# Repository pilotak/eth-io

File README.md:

# ETH IO
ESP32 based ethernet I/O board for home automation compatible with ESPHome, Tasmota, etc.

**Features**:
- wide range of input voltage 6-28V
- 4x opto-isolated "fast" operation inputs (connected to GPIO)
- 16x opto-isolated general inputs (connected to MCP23017 expander)
- 2x PWM capable low-side fully protected switches (connected to GPIO)
- 16x low-side fully protected switches for switching the non-latching relays or SSR relays (connected to MCP23017 expander)
- daisy chain design - see below

## Basic wiring

## "Fast" inputs
Are meant to be used for reading pulses from utility meter ie. power meter with S0 output

## Daisy chain design
Should you need more inputs/outputs (up to 96 more inputs/outputs or combination thanks to changing the address of MCP23017) you can use the same PCB. Just don't populate ETH breakout board and ESP32 and solder AMS1117-3.3 with its capacitor. The boards will be connected via SDA/SCL but thanks to a bus buffer (P82B96) communication can easilly be made up to 20 meters (possibly more by reducing speed of I2C bus)!
> In this mode the "slave" device can't make use of S0 inputs nor the PWM outputs

_For more information please visit [wiki](https://github.com/pilotak/eth-io/wiki)_

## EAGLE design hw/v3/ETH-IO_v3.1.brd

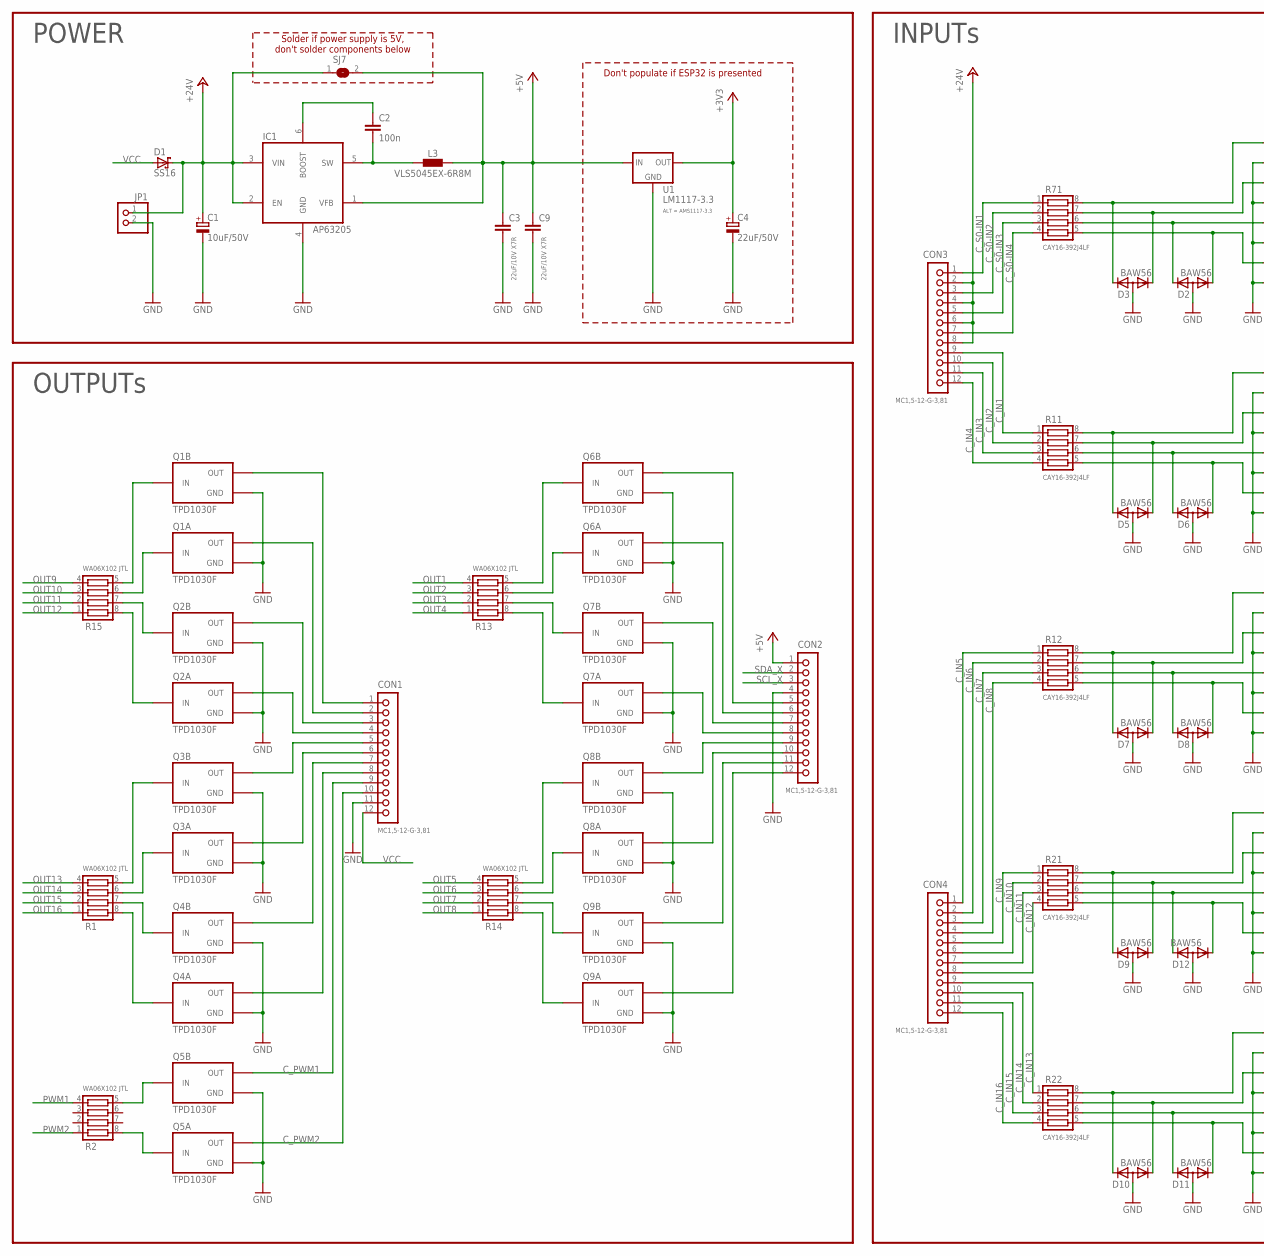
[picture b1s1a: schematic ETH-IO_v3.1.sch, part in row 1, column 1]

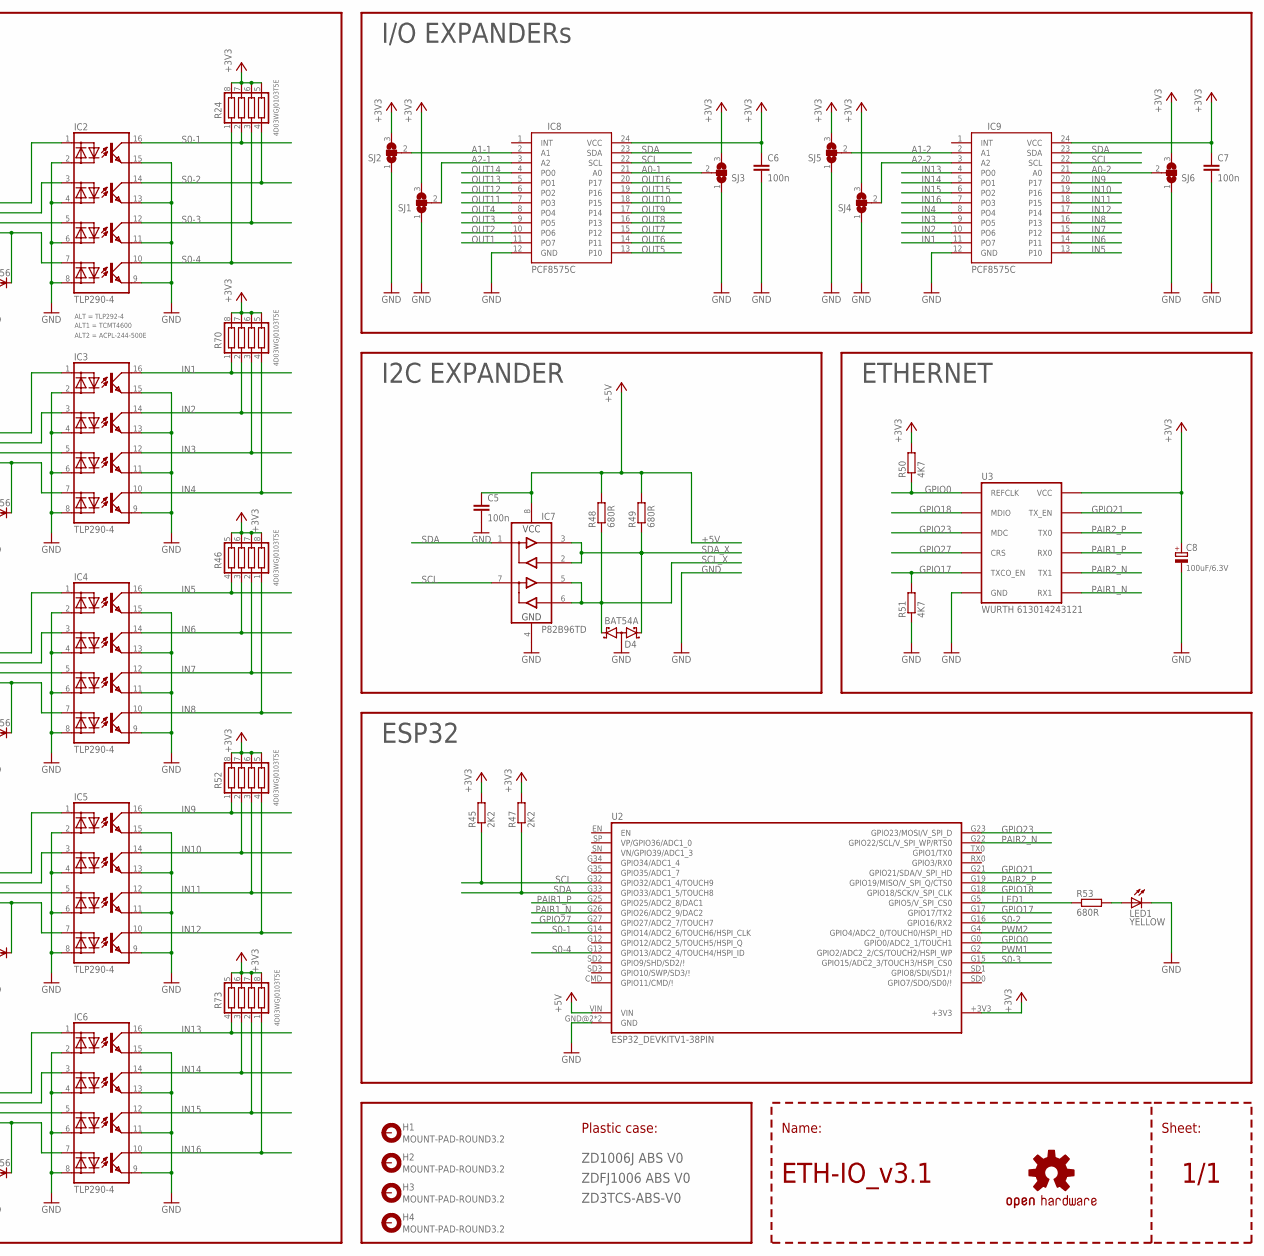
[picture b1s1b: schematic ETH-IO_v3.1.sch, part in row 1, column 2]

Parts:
C1: 10uF/50V; PANASONIC_C
C2, C5, C6, C7: 100n; C0805
C3, C9: 22uF/10V X7R; C1206
C4: 22uF/50V; PANASONIC_C
C8: 100uF/6.3V; PANASONIC_C
CON1, CON2, CON3, CON4: MC1,5-12-G-3,81; MC1,5/12-G-3,81
D1: SS16; DO214AC
D2, D3, D5, D6, D7, D8, D9, D10, D11, D12: BAW56; SOT23
D4: BAT54A; SOT23
H1, H2, H3, H4: MOUNT-PAD-ROUND3.2; 3,2-PAD
IC1: AP63205; SOT23-6
IC2, IC3, IC4, IC5, IC6: TLP290-4; SO16
IC7: P82B96TD; SO08
IC8, IC9: PCF8575C; SO-24DW
JP1: PINHD-1X2; 1X02
L3: VLS5045EX-6R8M; L5040-LONGER
LED1: YELLOW; LED0805
LOGO1: OSHW-LOGOM-COPPER; OSHW-LOGO-M_COPPER
Q1, Q2, Q3, Q4, Q5, Q6, Q7, Q8, Q9: TPD1030F; SO8
R1, R2, R13, R14, R15: WA06X102 JTL; RESCAV80P320X160X60-8N
R11, R12, R21, R22, R71: CAY16-392J4LF; RESCAV80P320X160X60-8N
R24, R46, R52, R70, R73: 4D03WGJ0103T5E; RESCAV80P320X160X60-8N
R45, R47: 2K2; R0805
R48, R49, R53: 680R; R0805
R50, R51: 4K7; R0805
SJ1, SJ2, SJ3, SJ4, SJ5, SJ6: SJ2W; SJ_2
SJ7: SJ
U1: LM1117-3.3; SOT223
U2: ESP32_DEVKITV1-38PIN; ESP32_DEVKITV1_38PIN
U3: WURTH 613014243121; LAN8720_ETH_BOARD

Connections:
+3V3: C4.+, C6.1, C7.1, C8.+, IC8.24 (VCC), IC9.24 (VCC), R24.5 (4), R24.6 (3), R24.7 (2), R24.8 (1), R45.2, R46.5 (4), R46.6 (3), R46.7 (2), R46.8 (1), R47.2, R50.2, R52.5 (4), R52.6 (3), R52.7 (2), R52.8 (1), R70.5 (4), R70.6 (3), R70.7 (2), R70.8 (1), R73.5 (4), R73.6 (3), R73.7 (2), R73.8 (1), SJ1.3, SJ2.3, SJ3.3, SJ4.3, SJ5.3, SJ6.3, U1.2 (OUT), U1.4 (OUT), U2.+3V3, U3.VCC, U3.VCC@1 (VCC)
+5V: C3.1, C5.1, C9.1, CON2.1, IC1.1 (VFB), IC7.8 (VCC), L3.1, R48.2, R49.2, SJ7.2, U1.3 (IN), U2.VIN
+24V: C1.+, CON3.2, CON3.4, CON3.6, CON3.8, D1.C, IC1.2 (EN), IC1.3 (VIN), JP1.1, SJ7.1
A0-1: IC8.21 (A0), SJ3.2
A0-2: IC9.21 (A0), SJ6.2
A1-1: IC8.2 (A1), SJ2.2
A1-2: IC9.2 (A1), SJ5.2
A2-1: IC8.3 (A2), SJ1.2
A2-2: IC9.3 (A2), SJ4.2
C_IN1: CON3.9, R11.1
C_IN2: CON3.10, R11.2
C_IN3: CON3.11, R11.3
C_IN4: CON3.12, R11.4
C_IN5: CON4.1, R12.1
C_IN6: CON4.2, R12.2
C_IN7: CON4.3, R12.3
C_IN8: CON4.4, R12.4
C_IN9: CON4.5, R21.1
C_IN10: CON4.6, R21.2
C_IN11: CON4.7, R21.3
C_IN12: CON4.8, R21.4
C_IN13: CON4.9, R22.1
C_IN14: CON4.10, R22.2
C_IN15: CON4.11, R22.3
C_IN16: CON4.12, R22.4
C_OUT1: CON2.5, Q6.5 (OUT), Q6.6 (OUT)
C_OUT2: CON2.6, Q6.7 (OUT), Q6.8 (OUT)
C_OUT3: CON2.7, Q7.5 (OUT), Q7.6 (OUT)
C_OUT4: CON2.8, Q7.7 (OUT), Q7.8 (OUT)
C_OUT5: CON2.9, Q8.5 (OUT), Q8.6 (OUT)
C_OUT6: CON2.10, Q8.7 (OUT), Q8.8 (OUT)
C_OUT7: CON2.11, Q9.5 (OUT), Q9.6 (OUT)
C_OUT8: CON2.12, Q9.7 (OUT), Q9.8 (OUT)
C_OUT9: CON1.1, Q1.5 (OUT), Q1.6 (OUT)
C_OUT10: CON1.2, Q1.7 (OUT), Q1.8 (OUT)
C_OUT11: CON1.3, Q2.5 (OUT), Q2.6 (OUT)
C_OUT12: CON1.4, Q2.7 (OUT), Q2.8 (OUT)
C_OUT13: CON1.5, Q3.5 (OUT), Q3.6 (OUT)
C_OUT14: CON1.6, Q3.7 (OUT), Q3.8 (OUT)
C_OUT15: CON1.7, Q4.5 (OUT), Q4.6 (OUT)
C_OUT16: CON1.8, Q4.7 (OUT), Q4.8 (OUT)
C_PWM1: CON1.9, Q5.5 (OUT), Q5.6 (OUT)
C_PWM2: CON1.10, Q5.7 (OUT), Q5.8 (OUT)
C_S0-IN1: CON3.1, R71.1
C_S0-IN2: CON3.3, R71.2
C_S0-IN3: CON3.5, R71.3
C_S0-IN4: CON3.7, R71.4
GND: C1.-, C3.2, C4.-, C5.2, C6.2, C7.2, C8.-, C9.2, CON1.11, CON2.4, D2.3 (A), D3.3 (A), D4.3 (AA), D5.3 (A), D6.3 (A), D7.3 (A), D8.3 (A), D9.3 (A), D10.3 (A), D11.3 (A), D12.3 (A), IC1.4 (GND), IC2.2 (C1), IC2.4 (C2), IC2.6 (C3), IC2.8 (C4), IC2.9 (EMIT4), IC2.11 (EMIT3), IC2.13 (EMIT2), IC2.15 (EMIT1), IC3.2 (C1), IC3.4 (C2), IC3.6 (C3), IC3.8 (C4), IC3.9 (EMIT4), IC3.11 (EMIT3), IC3.13 (EMIT2), IC3.15 (EMIT1), IC4.2 (C1), IC4.4 (C2), IC4.6 (C3), IC4.8 (C4), IC4.9 (EMIT4), IC4.11 (EMIT3), IC4.13 (EMIT2), IC4.15 (EMIT1), IC5.2 (C1), IC5.4 (C2), IC5.6 (C3), IC5.8 (C4), IC5.9 (EMIT4), IC5.11 (EMIT3), IC5.13 (EMIT2), IC5.15 (EMIT1), IC6.2 (C1), IC6.4 (C2), IC6.6 (C3), IC6.8 (C4), IC6.9 (EMIT4), IC6.11 (EMIT3), IC6.13 (EMIT2), IC6.15 (EMIT1), IC7.4 (GND), IC8.12 (GND), IC9.12 (GND), JP1.2, LED1.C, Q1.1 (GND), Q1.3 (GND), Q2.1 (GND), Q2.3 (GND), Q3.1 (GND), Q3.3 (GND), Q4.1 (GND), Q4.3 (GND), Q5.1 (GND), Q5.3 (GND), Q6.1 (GND), Q6.3 (GND), Q7.1 (GND), Q7.3 (GND), Q8.1 (GND), Q8.3 (GND), Q9.1 (GND), Q9.3 (GND), R51.1, SJ1.1, SJ2.1, SJ3.1, SJ4.1, SJ5.1, SJ6.1, U1.1 (GND), U2.GND@2 (GND), U2.GND@3 (GND), U3.GND, U3.GND@1 (GND)
GPIO0: R50.1, U2.G0 (GPIO0/ADC2_1/TOUCH1), U3.INT (REFCLK)
GPIO17: R51.2, U2.G17 (GPIO17/TX2), U3.TXCO_EN
GPIO18: U2.G18 (GPIO18/SCK/V_SPI_CLK), U3.MDIO
GPIO21: U2.G21 (GPIO21/SDA/V_SPI_HD), U3.TX_EN
GPIO23: U2.G23 (GPIO23/MOSI/V_SPI_D), U3.MDC
GPIO27: U2.G27 (GPIO27/ADC2_7/TOUCH7), U3.CRS
IN1: IC3.16 (COL1), IC9.11 (PO7), R70.1
IN2: IC3.14 (COL2), IC9.10 (PO6), R70.2
IN3: IC3.12 (COL3), IC9.9 (PO5), R70.3
IN4: IC3.10 (COL4), IC9.8 (PO4), R70.4
IN5: IC4.16 (COL1), IC9.13 (P10), R46.4
IN6: IC4.14 (COL2), IC9.14 (P11), R46.3
IN7: IC4.12 (COL3), IC9.15 (P12), R46.2
IN8: IC4.10 (COL4), IC9.16 (P13), R46.1
IN9: IC5.16 (COL1), IC9.20 (P17), R52.1
IN10: IC5.14 (COL2), IC9.19 (P16), R52.2
IN11: IC5.12 (COL3), IC9.18 (P15), R52.3
IN12: IC5.10 (COL4), IC9.17 (P14), R52.4
IN13: IC6.16 (COL1), IC9.4 (PO0), R73.4
IN14: IC6.14 (COL2), IC9.5 (PO1), R73.3
IN15: IC6.12 (COL3), IC9.6 (PO2), R73.2
IN16: IC6.10 (COL4), IC9.7 (PO3), R73.1
LED1: R53.1, U2.G5 (GPIO5/V_SPI_CS0)
LED_RED: LED1.A, R53.2
unnamed: D3.2 (K2), IC2.1 (A1), R71.8 (1)
unnamed: D3.1 (K1), IC2.3 (A2), R71.7 (2)
unnamed: Q1.2 (IN), R15.6 (3)
unnamed: Q1.4 (IN), R15.5 (4)
unnamed: D2.2 (K2), IC2.5 (A3), R71.6 (3)
unnamed: D2.1 (K1), IC2.7 (A4), R71.5 (4)
unnamed: D5.2 (K2), IC3.1 (A1), R11.8 (1)
unnamed: Q5.4 (IN), R2.5 (4)
unnamed: Q5.2 (IN), R2.8 (1)
unnamed: D6.1 (K1), IC3.7 (A4), R11.5 (4)
unnamed: D5.1 (K1), IC3.3 (A2), R11.7 (2)
unnamed: D6.2 (K2), IC3.5 (A3), R11.6 (3)
unnamed: D7.2 (K2), IC4.1 (A1), R12.8 (1)
unnamed: D7.1 (K1), IC4.3 (A2), R12.7 (2)
unnamed: D8.2 (K2), IC4.5 (A3), R12.6 (3)
unnamed: D8.1 (K1), IC4.7 (A4), R12.5 (4)
unnamed: D12.2 (K2), IC5.5 (A3), R21.6 (3)
unnamed: D12.1 (K1), IC5.7 (A4), R21.5 (4)
unnamed: D9.1 (K1), IC5.3 (A2), R21.7 (2)
unnamed: D9.2 (K2), IC5.1 (A1), R21.8 (1)
unnamed: D11.2 (K2), IC6.5 (A3), R22.6 (3)
unnamed: D11.1 (K1), IC6.7 (A4), R22.5 (4)
unnamed: D10.1 (K1), IC6.3 (A2), R22.7 (2)
unnamed: D10.2 (K2), IC6.1 (A1), R22.8 (1)
unnamed: Q2.4 (IN), R15.7 (2)
unnamed: Q2.2 (IN), R15.8 (1)
unnamed: Q3.4 (IN), R1.5 (4)
unnamed: Q3.2 (IN), R1.6 (3)
unnamed: Q4.4 (IN), R1.7 (2)
unnamed: Q4.2 (IN), R1.8 (1)
unnamed: Q6.4 (IN), R13.5 (4)
unnamed: Q6.2 (IN), R13.6 (3)
unnamed: Q7.4 (IN), R13.7 (2)
unnamed: Q7.2 (IN), R13.8 (1)
unnamed: Q8.4 (IN), R14.5 (4)
unnamed: Q8.2 (IN), R14.6 (3)
unnamed: Q9.4 (IN), R14.7 (2)
unnamed: Q9.2 (IN), R14.8 (1)
unnamed: C2.2, IC1.5 (SW), L3.2
unnamed: C2.1, IC1.6 (BOOST)
OUT1: IC8.11 (PO7), R13.4
OUT2: IC8.10 (PO6), R13.3
OUT3: IC8.9 (PO5), R13.2
OUT4: IC8.8 (PO4), R13.1
OUT5: IC8.13 (P10), R14.4
OUT6: IC8.14 (P11), R14.3
OUT7: IC8.15 (P12), R14.2
OUT8: IC8.16 (P13), R14.1
OUT9: IC8.17 (P14), R15.4
OUT10: IC8.18 (P15), R15.3
OUT11: IC8.7 (PO3), R15.2
OUT12: IC8.6 (PO2), R15.1
OUT13: IC8.5 (PO1), R1.4
OUT14: IC8.4 (PO0), R1.3
OUT15: IC8.19 (P16), R1.2
OUT16: IC8.20 (P17), R1.1
PAIR1_N: U2.G26 (GPIO26/ADC2_9/DAC2), U3.RX1
PAIR1_P: U2.G25 (GPIO25/ADC2_8/DAC1), U3.RX0
PAIR2_N: U2.G22 (GPIO22/SCL/V_SPI_WP/RTS0), U3.TX1
PAIR2_P: U2.G19 (GPIO19/MISO/V_SPI_Q/CTS0), U3.TX0
PWM1: R2.4, U2.G2 (GPIO2/ADC2_2/CS/TOUCH2/HSPI_WP)
PWM2: R2.1, U2.G4 (GPIO4/ADC2_0/TOUCH0/HSPI_HD)
S0-1: IC2.16 (COL1), R24.2, U2.G14 (GPIO14/ADC2_6/TOUCH6/HSPI_CLK)
S0-2: IC2.14 (COL2), R24.4, U2.G16 (GPIO16/RX2)
S0-3: IC2.12 (COL3), R24.3, U2.G15 (GPIO15/ADC2_3/TOUCH3/HSPI_CS0)
S0-4: IC2.10 (COL4), R24.1, U2.G13 (GPIO13/ADC2_4/TOUCH4/HSPI_ID)
SCL: IC7.7 (SY), IC8.22 (SCL), IC9.22 (SCL), R45.1, U2.G32 (GPIO32/ADC1_4/TOUCH9)
SCL_X: CON2.3, D4.1 (K1), IC7.5 (TY), IC7.6 (RY), R48.1
SDA: IC7.1 (SX), IC8.23 (SDA), IC9.23 (SDA), R47.1, U2.G33 (GPIO33/ADC1_5/TOUCH8)
SDA_X: CON2.2, D4.2 (K2), IC7.2 (RX), IC7.3 (TX), R49.1
VCC: CON1.12, D1.A

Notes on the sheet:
INPUTs
OUTPUTs
POWER
I2C EXPANDER
ETHERNET
ZDFJ1006 ABS V0
ZD3TCS-ABS-V0
ZD1006J ABS V0
Don't populate if ESP32 is presented
ESP32
ETH-IO_v3.1
Sheet:
Name:
Plastic case:
I/O EXPANDERs
Solder if power supply is 5V, don't solder components below

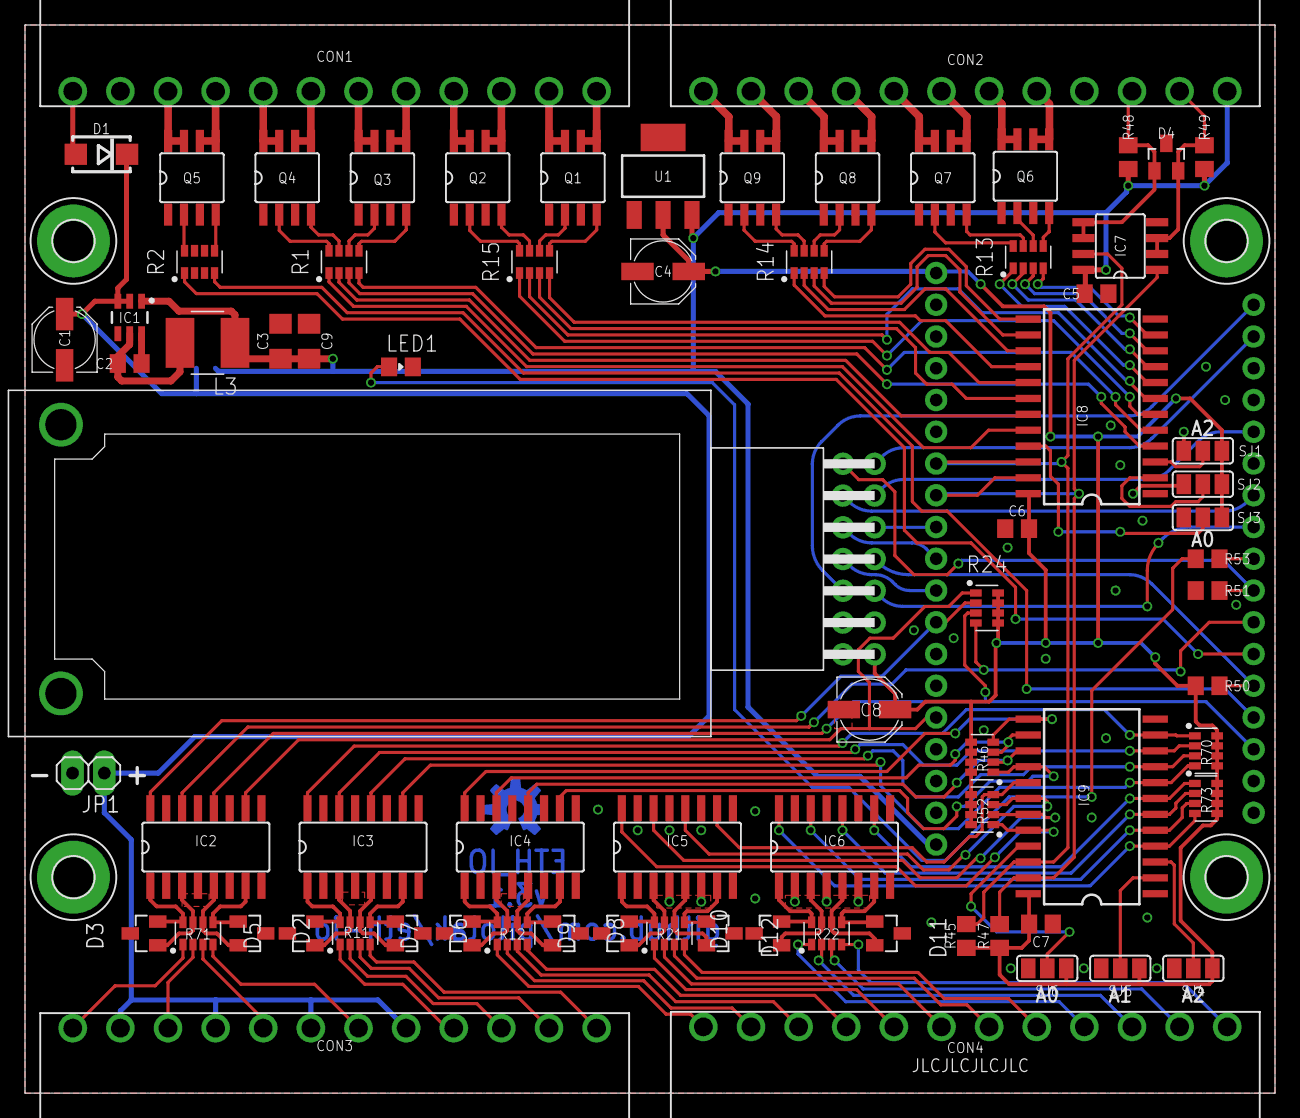
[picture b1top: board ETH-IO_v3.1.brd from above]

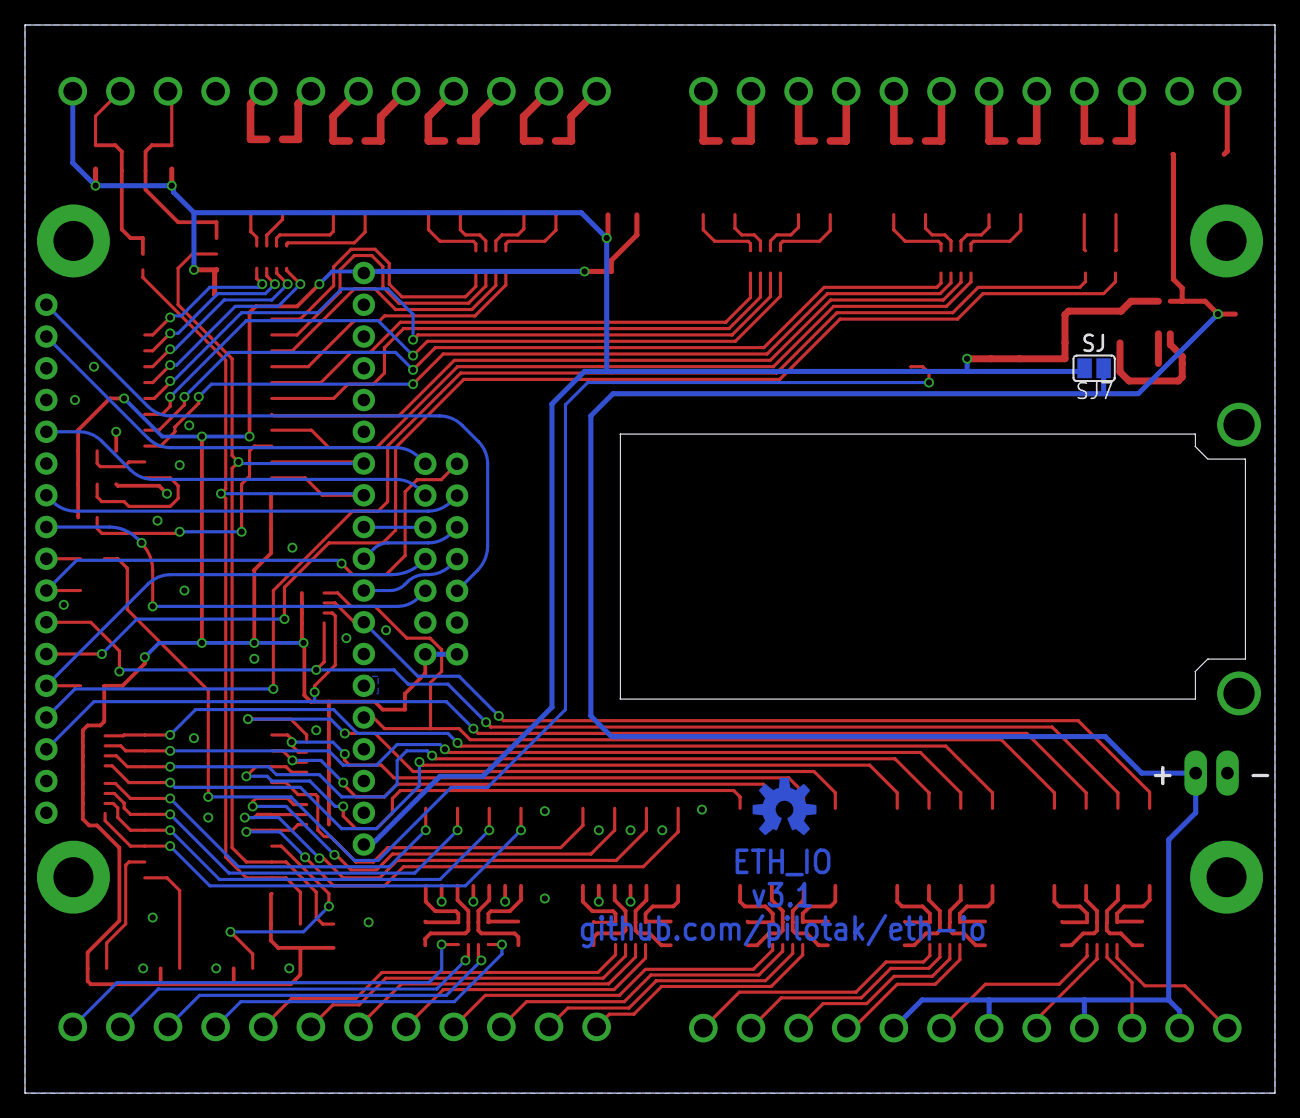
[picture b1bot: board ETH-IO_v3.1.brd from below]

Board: 2 copper layers, 100.0 x 85.4 mm, 83 parts (2 on the bottom side), 143 nets.

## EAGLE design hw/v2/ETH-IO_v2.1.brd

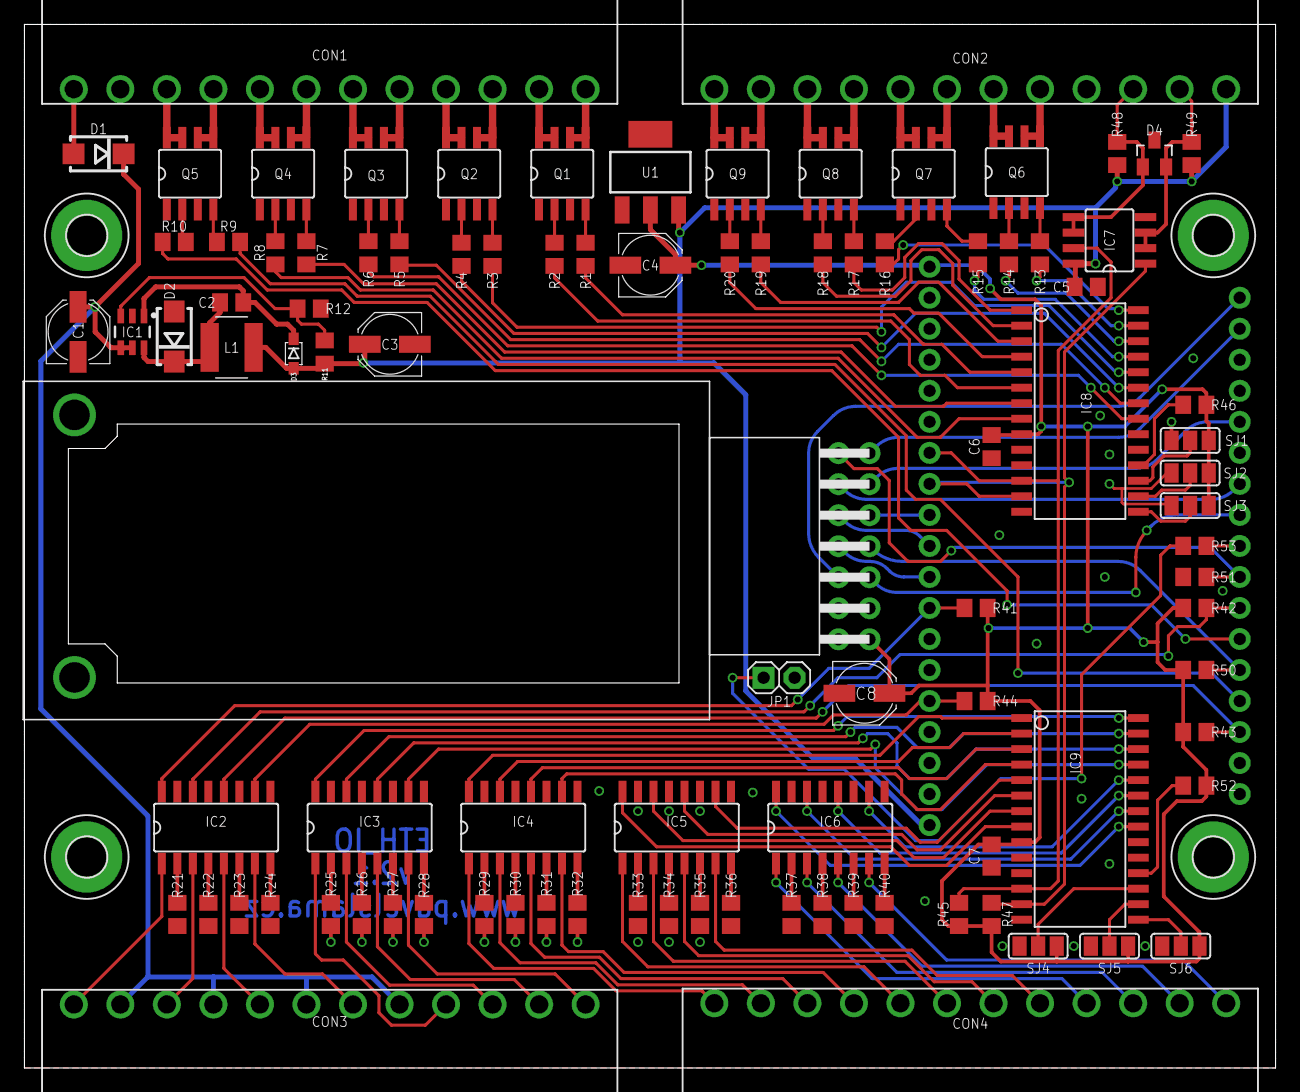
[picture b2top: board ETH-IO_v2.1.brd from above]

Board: 2 copper layers, 102.4 x 85.4 mm, 102 parts (0 on the bottom side), 146 nets.

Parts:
C1, C3, C4: 22uF/50V; PANASONIC_C
C2, C5, C6, C7: 100n; C0805
C8: 100uF/6.3V; PANASONIC_C
CON1, CON2, CON3, CON4: MC1,5-12-G-3,81; MC1,5/12-G-3,81
D1, D2: SS16; DO214AC
D3: 1N4148WS; SOD323
D4: BAT54A; SOT23
H1, H2, H3, H4: MOUNT-PAD-ROUND3.2; 3,2-PAD
IC1: MCP16301T-I/CH; SOT23-6
IC2, IC3, IC4, IC5, IC6: TLP290-4; SO16
IC7: P82B96TD; SO08
IC8, IC9: MCP23017-E/SO; SO28W
JP1: 1X02-S
L1: SRN5040-220M; L5040
Q1, Q2, Q3, Q4, Q5, Q6, Q7, Q8, Q9: BTS3410G; SO8
R1, R2, R3, R4, R5, R6, R7, R8, R9, R10, R13, R14, R15, R16, R17, R18, R19, R20, R46, R52: 1K; R0805
R11: 52K3; R0805
R12: 10K 1%; R0805
R21, R22, R23, R24, R25, R26, R27, R28, R29, R30, R31, R32, R33, R34, R35, R36, R37, R38, R39, R40: 3K9; R0805
R41, R42, R43, R44: 10K; R0805
R45, R47: 2K2; R0805
R48, R49, R53: 680R; R0805
R50, R51: 4K7; R0805
SJ1, SJ2, SJ3, SJ4, SJ5, SJ6: SJ_2
U1: LM1117-3.3; SOT223
U2: ESP32_DEVKITV1-38PIN; ESP32_DEVKITV1_38PIN
U3: WURTH 613014243121; LAN8720_ETH_BOARD

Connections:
+3V3: C4.+, C6.1, C7.1, C8.+, IC8.9, IC9.9, R41.2, R42.2, R43.2, R44.2, R45.2, R46.2, R47.2, R50.2, R52.2, SJ1.3, SJ2.3, SJ3.3, SJ4.3, SJ5.3, SJ6.3, U1.2, U1.4, U2.+3V3, U3.VCC, U3.VCC@1
+5V: C3.+, C5.1, CON2.1, D3.A, IC7.8, L1.1, R11.2, R48.2, R49.2, U1.3, U2.VIN
+24V: C1.+, CON3.2, CON3.4, CON3.6, CON3.8, D1.C, IC1.4, IC1.5
C_IN1: CON3.9, IC3.1
C_IN2: CON3.10, IC3.3
C_IN3: CON3.11, IC3.5
C_IN4: CON3.12, IC3.7
C_IN5: CON4.1, IC4.1
C_IN6: CON4.2, IC4.3
C_IN7: CON4.3, IC4.5
C_IN8: CON4.4, IC4.7
C_IN9: CON4.5, IC5.1
C_IN10: CON4.6, IC5.3
C_IN11: CON4.7, IC5.5
C_IN12: CON4.8, IC5.7
C_IN13: CON4.9, IC6.1
C_IN14: CON4.10, IC6.3
C_IN15: CON4.11, IC6.5
C_IN16: CON4.12, IC6.7
C_OUT1: CON2.5, Q6.5, Q6.6
C_OUT2: CON2.6, Q6.7, Q6.8
C_OUT3: CON2.7, Q7.5, Q7.6
C_OUT4: CON2.8, Q7.7, Q7.8
C_OUT5: CON2.9, Q8.5, Q8.6
C_OUT6: CON2.10, Q8.7, Q8.8
C_OUT7: CON2.11, Q9.5, Q9.6
C_OUT8: CON2.12, Q9.7, Q9.8
C_OUT9: CON1.1, Q1.5, Q1.6
C_OUT10: CON1.2, Q1.7, Q1.8
C_OUT11: CON1.3, Q2.5, Q2.6
C_OUT12: CON1.4, Q2.7, Q2.8
C_OUT13: CON1.5, Q3.5, Q3.6
C_OUT14: CON1.6, Q3.7, Q3.8
C_OUT15: CON1.7, Q4.5, Q4.6
C_OUT16: CON1.8, Q4.7, Q4.8
C_PWM1: CON1.9, Q5.5, Q5.6
C_PWM2: CON1.10, Q5.7, Q5.8
C_S0-IN1: CON3.1, IC2.1
C_S0-IN2: CON3.3, IC2.3
C_S0-IN3: CON3.5, IC2.5
C_S0-IN4: CON3.7, IC2.7
GND: C1.-, C3.-, C4.-, C5.2, C6.2, C7.2, C8.-, CON1.11, CON2.4, D2.A, D4.3, IC1.2, IC2.9, IC2.11, IC2.13, IC2.15, IC3.9, IC3.11, IC3.13, IC3.15, IC4.9, IC4.11, IC4.13, IC4.15, IC5.9, IC5.11, IC5.13, IC5.15, IC6.9, IC6.11, IC6.13, IC6.15, IC7.4, IC8.10, IC9.10, JP1.2, Q1.1, Q1.3, Q2.1, Q2.3, Q3.1, Q3.3, Q4.1, Q4.3, Q5.1, Q5.3, Q6.1, Q6.3, Q7.1, Q7.3, Q8.1, Q8.3, Q9.1, Q9.3, R12.1, R21.1, R22.1, R23.1, R24.1, R25.1, R26.1, R27.1, R28.1, R29.1, R30.1, R31.1, R32.1, R33.1, R34.1, R35.1, R36.1, R37.1, R38.1, R39.1, R40.1, R51.1, SJ1.1, SJ2.1, SJ3.1, SJ4.1, SJ5.1, SJ6.1, U1.1, U2.GND@2, U2.GND@3, U3.GND, U3.GND@1
GPIO0: R50.1, U2.G0, U3.INT
GPIO17: R51.2, U2.G17, U3.TXCO_EN
GPIO18: U2.G18, U3.MDIO
GPIO21: U2.G21, U3.TX_EN
GPIO23: U2.G23, U3.MDC
GPIO27: U2.G27, U3.CRS
IN1: IC3.16, IC9.28
IN2: IC3.14, IC9.27
IN3: IC3.12, IC9.26
IN4: IC3.10, IC9.25
IN5: IC4.16, IC9.1
IN6: IC4.14, IC9.2
IN7: IC4.12, IC9.3
IN8: IC4.10, IC9.4
IN9: IC5.16, IC9.8
IN10: IC5.14, IC9.7
IN11: IC5.12, IC9.6
IN12: IC5.10, IC9.5
IN13: IC6.16, IC9.21
IN14: IC6.14, IC9.22
IN15: IC6.12, IC9.23
IN16: IC6.10, IC9.24
LED1: R53.1, U2.G5
LED_RED: JP1.1, R53.2
unnamed: IC9.15, SJ6.2
unnamed: IC8.16, SJ2.2
unnamed: Q1.2, R2.2
unnamed: Q1.4, R1.2
unnamed: IC8.18, R46.1
unnamed: IC9.18, R52.1
unnamed: IC8.15, SJ3.2
unnamed: Q5.4, R9.2
unnamed: Q5.2, R10.2
unnamed: IC9.16, SJ5.2
unnamed: IC3.2, R25.2
unnamed: IC3.4, R26.2
unnamed: IC3.6, R27.2
unnamed: IC3.8, R28.2
unnamed: IC4.2, R29.2
unnamed: IC4.4, R30.2
unnamed: IC4.6, R31.2
unnamed: IC4.8, R32.2
unnamed: IC5.2, R33.2
unnamed: IC5.4, R34.2
unnamed: IC5.6, R35.2
unnamed: IC5.8, R36.2
unnamed: IC6.2, R37.2
unnamed: IC6.4, R38.2
unnamed: IC6.6, R39.2
unnamed: IC6.8, R40.2
unnamed: IC9.17, SJ4.2
unnamed: Q2.4, R3.2
unnamed: Q2.2, R4.2
unnamed: IC8.17, SJ1.2
unnamed: Q3.4, R5.2
unnamed: Q3.2, R6.2
unnamed: Q4.4, R7.2
unnamed: Q4.2, R8.2
unnamed: IC2.2, R21.2
unnamed: Q6.4, R13.2
unnamed: Q6.2, R14.2
unnamed: Q7.4, R15.2
unnamed: Q7.2, R16.2
unnamed: Q8.4, R17.2
unnamed: Q8.2, R18.2
unnamed: Q9.4, R19.2
unnamed: Q9.2, R20.2
unnamed: IC2.4, R22.2
unnamed: IC2.6, R23.2
unnamed: IC2.8, R24.2
unnamed: C2.2, D2.C, IC1.6, L1.2
unnamed: C2.1, D3.C, IC1.1
unnamed: IC1.3, R11.1, R12.2
OUT1: IC8.27, R13.1
OUT2: IC8.26, R14.1
OUT3: IC8.25, R15.1
OUT4: IC8.28, R16.1
OUT5: IC8.1, R17.1
OUT6: IC8.2, R18.1
OUT7: IC8.3, R19.1
OUT8: IC8.4, R20.1
OUT9: IC8.5, R1.1
OUT10: IC8.6, R2.1
OUT11: IC8.24, R3.1
OUT12: IC8.23, R4.1
OUT13: IC8.22, R5.1
OUT14: IC8.21, R6.1
OUT15: IC8.7, R7.1
OUT16: IC8.8, R8.1
PAIR1_N: U2.G26, U3.RX1
PAIR1_P: U2.G25, U3.RX0
PAIR2_N: U2.G22, U3.TX1
PAIR2_P: U2.G19, U3.TX0
PWM1: R9.1, U2.G2
PWM2: R10.1, U2.G4
S0-1: IC2.16, R41.1, U2.G14
S0-2: IC2.14, R42.1, U2.G16
S0-3: IC2.12, R43.1, U2.G15
S0-4: IC2.10, R44.1, U2.G13
SCL: IC7.7, IC8.12, IC9.12, R45.1, U2.G32
SCL_X: CON2.3, D4.1, IC7.5, IC7.6, R48.1
SDA: IC7.1, IC8.13, IC9.13, R47.1, U2.G33
SDA_X: CON2.2, D4.2, IC7.2, IC7.3, R49.1
VCC: CON1.12, D1.A

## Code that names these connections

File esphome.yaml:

esphome:
  name: eth_io
  platform: ESP32
  board: nodemcu-32s

ethernet:
  type: LAN8720
  mdc_pin: GPIO23
  mdio_pin: GPIO18
  phy_addr: 1
  clk_mode: GPIO0_IN
  power_pin: GPIO17

logger:

ota:

api:

i2c:
  sda: GPIO33
  scl: GPIO32
  frequency: 100kHz

mcp23017:
  - id: out_hub1
    address: 0x20

  - id: in_hub1
    address: 0x21

time:
  - platform: homeassistant
    id: homeassistant_time
    timezone: "Europe/Prague"

status_led:
  pin:
    number: GPIO5

sensor:
  - platform: pulse_counter
    pin: GPIO14
    name: "Power consumption 1"
    id: power1
    unit_of_measurement: 'Wh'
    internal_filter: 13us
    filters:
      - multiply: 16.66666666666
    count_mode:
      rising_edge: DISABLE
      falling_edge: INCREMENT

  - platform: pulse_counter
    pin: GPIO16
    name: "Power consumption 2"
    id: power2
    unit_of_measurement: 'Wh'
    internal_filter: 13us
    filters:
      - multiply: 16.66666666666
    count_mode:
      rising_edge: DISABLE
      falling_edge: INCREMENT

  - platform: pulse_counter
    pin: GPIO15
    name: "Power consumption 3"
    id: power3
    unit_of_measurement: 'Wh'
    internal_filter: 13us
    filters:
      - multiply: 16.66666666666
    count_mode:
      rising_edge: DISABLE
      falling_edge: INCREMENT

  - platform: pulse_counter
    pin: GPIO13
    name: "Power consumption 4"
    id: power4
    unit_of_measurement: 'Wh'
    internal_filter: 13us
    filters:
      - multiply: 16.66666666666
    count_mode:
      rising_edge: DISABLE
      falling_edge: INCREMENT

  - platform: total_daily_energy
    name: "Daily power consumption 1"
    icon: "mdi:current-ac"
    power_id: power1
    unit_of_measurement: 'kWh'
    filters:
      - multiply: 0.001

  - platform: total_daily_energy
    name: "Daily power consumption 2"
    icon: "mdi:current-ac"
    power_id: power2
    unit_of_measurement: 'kWh'
    filters:
      - multiply: 0.001

  - platform: total_daily_energy
    name: "Daily power consumption 3"
    icon: "mdi:current-ac"
    power_id: power3
    unit_of_measurement: 'kWh'
    filters:
      - multiply: 0.001

  - platform: total_daily_energy
    name: "Daily power consumption 4"
    icon: "mdi:current-ac"
    power_id: power4
    unit_of_measurement: 'kWh'
    filters:
      - multiply: 0.001

binary_sensor:
  - platform: gpio
    id: in1
    pin:
      mcp23017: in_hub1
      number: 7
      mode: INPUT_PULLUP
      inverted: True
    filters:
      - delayed_on: 3ms
      - delayed_off: 3ms
    on_click:
      then:
        - switch.toggle: output1

  - platform: gpio
    id: in2
    pin:
      mcp23017: in_hub1
      number: 6
      mode: INPUT_PULLUP
      inverted: True
    filters:
      - delayed_on: 3ms
      - delayed_off: 3ms
    on_click:
      then:
        - switch.toggle: output2

  - platform: gpio
    id: in3
    pin:
      mcp23017: in_hub1
      number: 5
      mode: INPUT_PULLUP
      inverted: True
    filters:
      - delayed_on: 3ms
      - delayed_off: 3ms
    on_click:
      then:
        - switch.toggle: output3

  - platform: gpio
    id: in4
    pin:
      mcp23017: in_hub1
      number: 4
      mode: INPUT_PULLUP
      inverted: True
    filters:
      - delayed_on: 3ms
      - delayed_off: 3ms
    on_click:
      then:
        - switch.toggle: output4

  - platform: gpio
    id: in5
    pin:
      mcp23017: in_hub1
      number: 8
      mode: INPUT_PULLUP
      inverted: True
    filters:
      - delayed_on: 3ms
      - delayed_off: 3ms
    on_click:
      then:
        - switch.toggle: output5

  - platform: gpio
    id: in6
    pin:
      mcp23017: in_hub1
      number: 9
      mode: INPUT_PULLUP
      inverted: True
    filters:
      - delayed_on: 3ms
      - delayed_off: 3ms
    on_click:
      then:
        - switch.toggle: output6

  - platform: gpio
    id: in7
    pin:
      mcp23017: in_hub1
      number: 10
      mode: INPUT_PULLUP
      inverted: True
    filters:
      - delayed_on: 3ms
      - delayed_off: 3ms
    on_click:
      then:
        - switch.toggle: output7

  - platform: gpio
    id: in8
    pin:
      mcp23017: in_hub1
      number: 11
      mode: INPUT_PULLUP
      inverted: True
    filters:
      - delayed_on: 3ms
      - delayed_off: 3ms
    on_click:
      then:
        - switch.toggle: output8

  - platform: gpio
    id: in9
    pin:
      mcp23017: in_hub1
      number: 15
      mode: INPUT_PULLUP
      inverted: True
    filters:
      - delayed_on: 3ms
      - delayed_off: 3ms
    on_click:
      then:
        - switch.toggle: output9

  - platform: gpio
    id: in10
    pin:
      mcp23017: in_hub1
      number: 14
      mode: INPUT_PULLUP
      inverted: True
    filters:
      - delayed_on: 3ms
      - delayed_off: 3ms
    on_click:
      then:
        - switch.toggle: output10

  - platform: gpio
    id: in11
    pin:
      mcp23017: in_hub1
      number: 13
      mode: INPUT_PULLUP
      inverted: True
    filters:
      - delayed_on: 3ms
      - delayed_off: 3ms
    on_click:
      then:
        - switch.toggle: output11

  - platform: gpio
    id: in12
    pin:
      mcp23017: in_hub1
      number: 12
      mode: INPUT_PULLUP
      inverted: True
    filters:
      - delayed_on: 3ms
      - delayed_off: 3ms
    on_click:
      then:
        - switch.toggle: output12

  - platform: gpio
    id: in13
    pin:
      mcp23017: in_hub1
      number: 0
      mode: INPUT_PULLUP
      inverted: True
    filters:
      - delayed_on: 3ms
      - delayed_off: 3ms
    on_click:
      then:
        - switch.toggle: output13

  - platform: gpio
    id: in14
    pin:
      mcp23017: in_hub1
      number: 1
      mode: INPUT_PULLUP
      inverted: True
    filters:
      - delayed_on: 3ms
      - delayed_off: 3ms
    on_click:
      then:
        - switch.toggle: output14

  - platform: gpio
    id: in15
    pin:
      mcp23017: in_hub1
      number: 2
      mode: INPUT_PULLUP
      inverted: True
    filters:
      - delayed_on: 3ms
      - delayed_off: 3ms
    on_click:
      then:
        - switch.toggle: output15

  - platform: gpio
    id: in16
    pin:
      mcp23017: in_hub1
      number: 3
      mode: INPUT_PULLUP
      inverted: True
    filters:
      - delayed_on: 3ms
      - delayed_off: 3ms
    on_click:
      then:
        - switch.toggle: output16

switch:
  - platform: gpio
    name: "PWM output 1"
    id: pwm1
    pin: GPIO2

  - platform: gpio
    name: "PWM output 2"
    id: pwm2
    pin: GPIO4

  - platform: gpio
    name: "Output 1"
    id: output1
    pin:
      mcp23017: out_hub1
      number: 6
      mode: OUTPUT
      inverted: False

  - platform: gpio
    name: "Output 2"
    id: output2
    pin:
      mcp23017: out_hub1
      number: 5
      mode: OUTPUT
      inverted: False

  - platform: gpio
    name: "Output 3"
    id: output3
    pin:
      mcp23017: out_hub1
      number: 4
      mode: OUTPUT
      inverted: False

  - platform: gpio
    name: "Output 4"
    id: output4
    pin:
      mcp23017: out_hub1
      number: 7
      mode: OUTPUT
      inverted: False

  - platform: gpio
    name: "Output 5"
    id: output5
    pin:
      mcp23017: out_hub1
      number: 8
      mode: OUTPUT
      inverted: False

  - platform: gpio
    name: "Output 6"
    id: output6
    pin:
      mcp23017: out_hub1
      number: 9
      mode: OUTPUT
      inverted: False

  - platform: gpio
    name: "Output 7"
    id: output7
    pin:
      mcp23017: out_hub1
      number: 10
      mode: OUTPUT
      inverted: False

  - platform: gpio
    name: "Output 8"
    id: output8
    pin:
      mcp23017: out_hub1
      number: 11
      mode: OUTPUT
      inverted: False

  - platform: gpio
    name: "Output 9"
    id: output9
    pin:
      mcp23017: out_hub1
      number: 12
      mode: OUTPUT
      inverted: False

  - platform: gpio
    name: "Output 10"
    id: output10
    pin:
      mcp23017: out_hub1
      number: 13
      mode: OUTPUT
      inverted: False

  - platform: gpio
    name: "Output 11"
    id: output11
    pin:
      mcp23017: out_hub1
      number: 3
      mode: OUTPUT
      inverted: False

  - platform: gpio
    name: "Output 12"
    id: output12
    pin:
      mcp23017: out_hub1
      number: 2
      mode: OUTPUT
      inverted: False

  - platform: gpio
    name: "Output 13"
    id: output13
    pin:
      mcp23017: out_hub1
      number: 1
      mode: OUTPUT
      inverted: False

  - platform: gpio
    name: "Output 14"
    id: output14
    pin:
      mcp23017: out_hub1
      number: 0
      mode: OUTPUT
      inverted: False

  - platform: gpio
    name: "Output 15"
    id: output15
    pin:
      mcp23017: out_hub1
      number: 14
      mode: OUTPUT
      inverted: False

  - platform: gpio
    name: "Output 16"
    id: output16
    pin:
      mcp23017: out_hub1
      number: 15
      mode: OUTPUT
      inverted: False

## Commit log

2021-03-20 init
2021-03-20 img update
2021-03-20 add logo
2021-03-20 center logo
2021-03-20 esphome config
2021-03-21 wiring diagrams
2021-03-21 daisy chain update
2021-04-26 assembly
2021-04-26 wiki link update
2021-05-29 restructure
2021-07-06 OSHW logo
2021-07-06 OSHW
2022-12-18 add v3 PCB
2022-12-19 bigger footprints
2022-12-19 added image of a jumper on a top side of the ethernet breakout board
2022-12-20 renamed assembly image
2022-12-20 Fixes #12 Added image of a jumper on the top of the eth board
    * added image of a jumper on a top side of the ethernet breakout board

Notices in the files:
parts and their libraries:
SparkFun-DigitalIC: Licensing: Creative Commons ShareAlike 4.0 International - https://creativecommons.org/licenses/by-sa/4.0
